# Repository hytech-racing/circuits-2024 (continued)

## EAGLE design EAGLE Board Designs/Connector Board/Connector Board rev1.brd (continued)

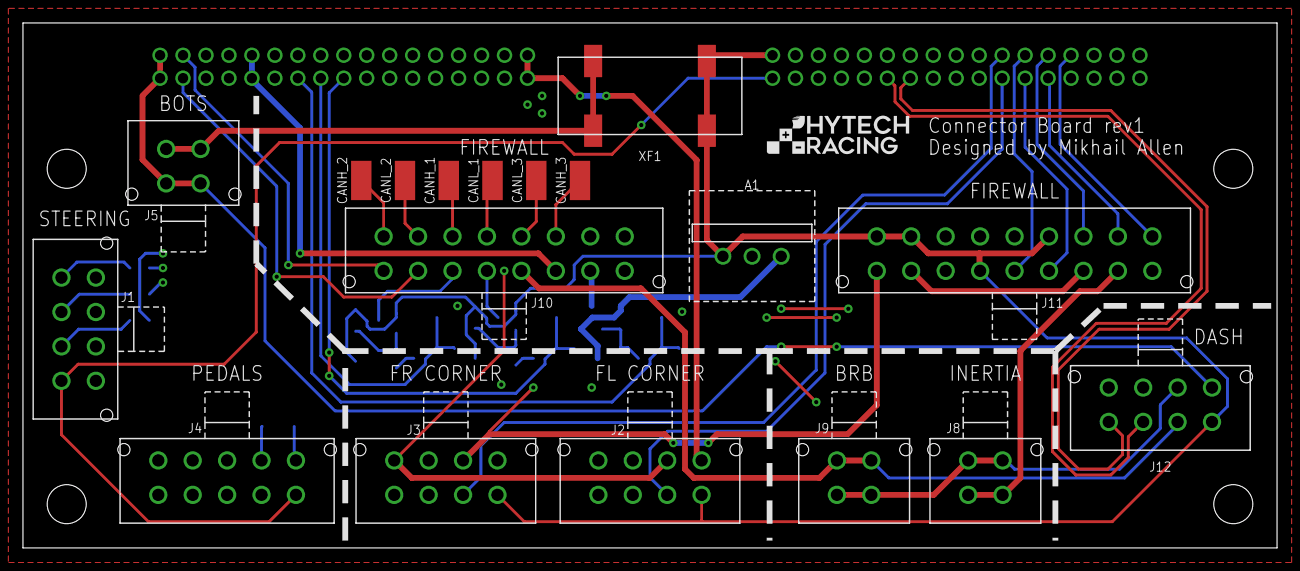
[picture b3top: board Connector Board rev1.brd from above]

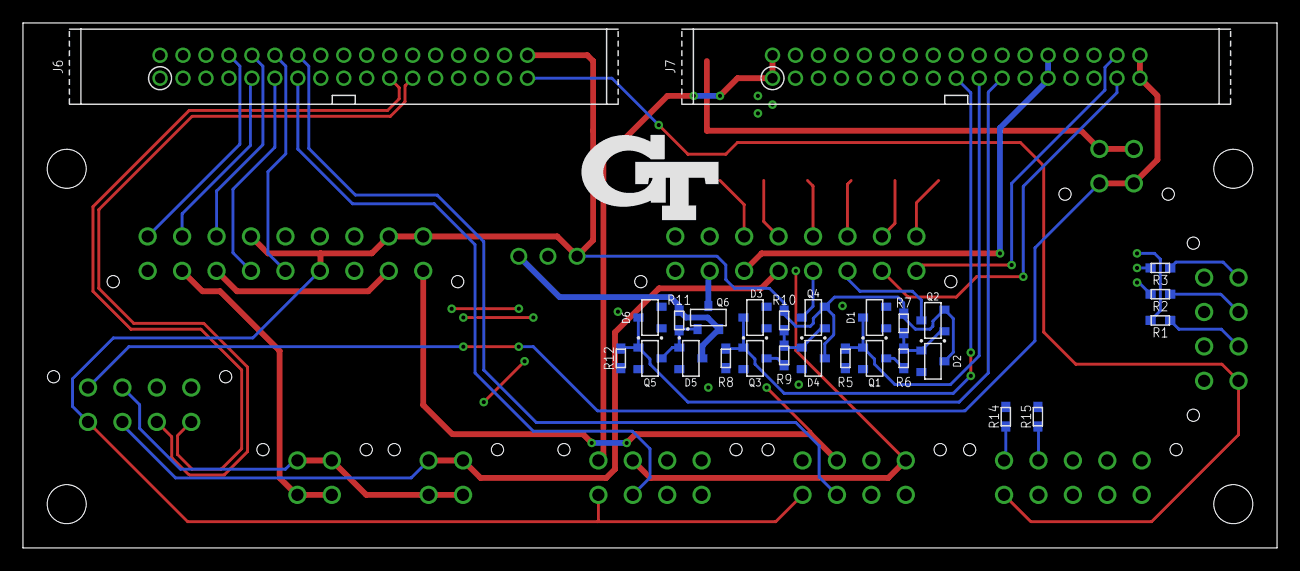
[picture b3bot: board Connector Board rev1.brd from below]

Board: 4 copper layers, 109.2 x 45.7 mm, 51 parts (28 on the bottom side), 59 nets.

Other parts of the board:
U$4, U$5, U$6, U$7: MOUNTING_M3
U$11: LOGO_GT_MEDIUM
U$14: LOGO_HYTECH_SMALL

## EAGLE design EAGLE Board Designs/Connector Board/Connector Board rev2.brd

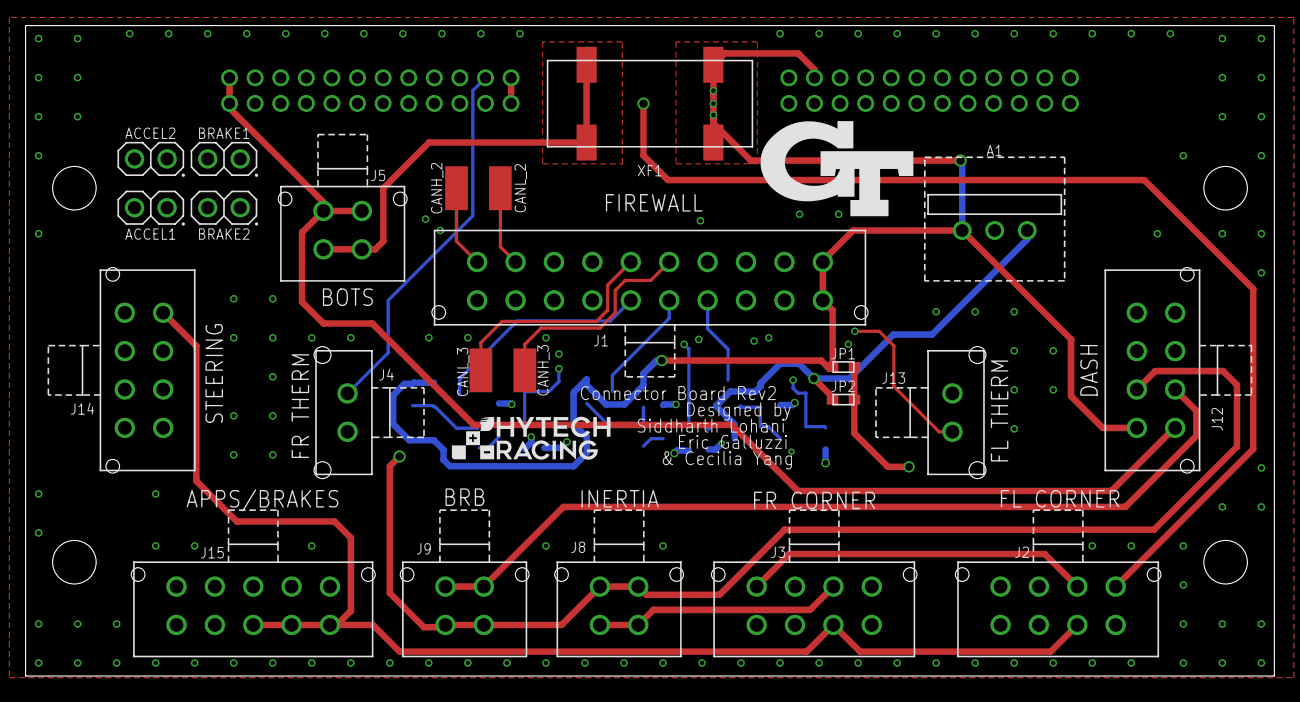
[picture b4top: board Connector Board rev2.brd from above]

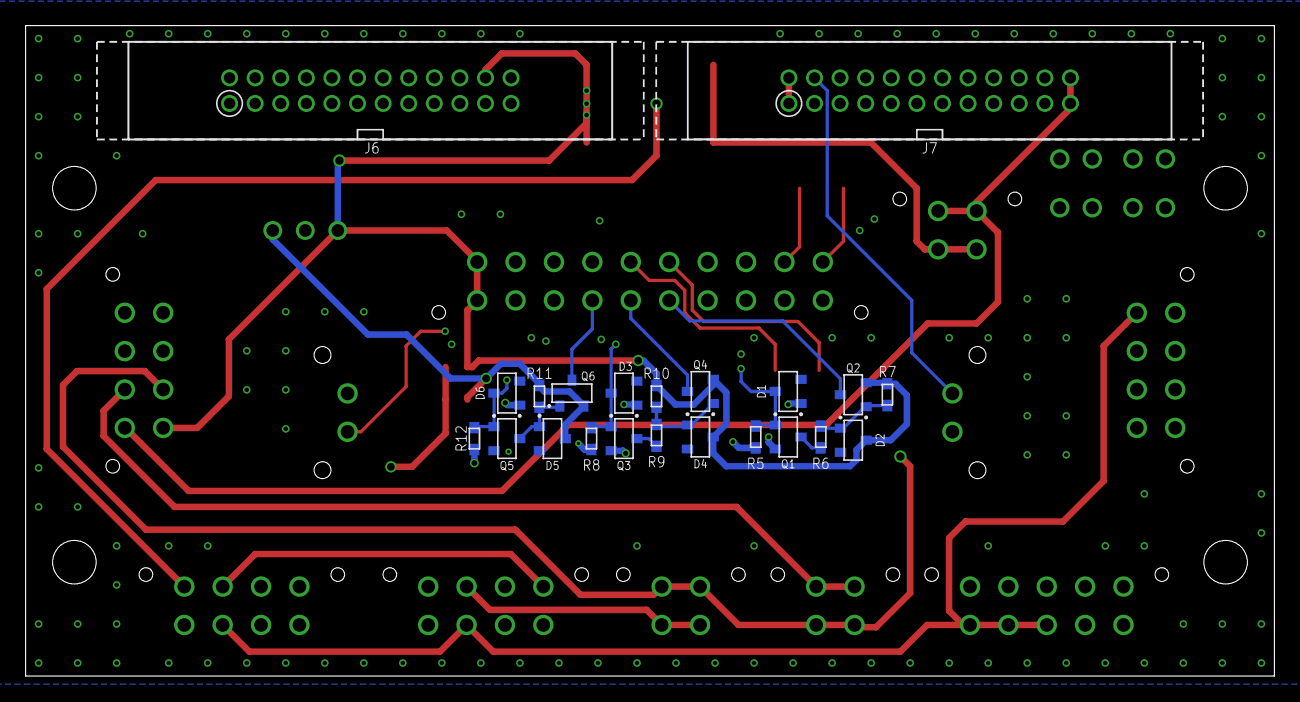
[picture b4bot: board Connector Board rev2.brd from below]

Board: 4 copper layers, 97.5 x 50.8 mm, 51 parts (22 on the bottom side), 52 nets.

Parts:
A1: VOLTAGE_REGULATOR_MODULE_OKI-78SR_12V; OKI-78SR
ACCEL1, ACCEL2: JUMPER__1X02; 1X02
BRAKE1, BRAKE2: JUMPER__1X02; 1X02
CANH_2, CANH_3: TEST_POINT; 5015
CANL_2, CANL_3: TEST_POINT; 5015
D1, D2, D3, D4, D5, D6: TVS__15V; SOT-23
J1: CONNECTOR-20_MF_T_V_; MOLEX_MICROFIT_PTH_VERTICAL_20_DUAL
J2, J3, J12, J14: CONNECTOR-8_μF_T_V_BLACK; MOLEX_MICROFIT_PTH_VERTICAL_08_DUAL
J4, J13: CONNECTOR-2_MF_T_V_; MOLEX_MICROFIT_PTH_VERTICAL_02_SINGLE
J5, J8, J9: CONNECTOR-4_μF_T_V_BLACK; MOLEX_MICROFIT_PTH_VERTICAL_04_DUAL
J6, J7: CONNECTOR-24_CONNECTOR-24_; EHT-112-01
J15: CONNECTOR-10_MF_T_V_; MOLEX_MICROFIT_PTH_VERTICAL_10_DUAL
JP1, JP2: JUMPER_0603_; 0603-RES
Q1, Q3, Q5: TRANSISTOR_N_MOS__DMG3406L-7; SOT-23
Q2, Q4, Q6: TRANSISTOR_P_MOS_SOT-23_DMP3056L-7; SOT-23
R5, R8, R11, R12: RESISTOR_0603_10K; 0603-RES
R6, R7, R9, R10: RESISTOR_0603_5.1K; 0603-RES
U$4, U$5, U$6, U$7: MOUNTING_M3
U$11: LOGO_GT_MEDIUM
U$14: LOGO_HYTECH_SMALL
XF1: FUSE_HOLDER_MINIBLADESMD; 3588

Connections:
+5V: J2.2, J3.2, J6.24, J14.1, J15.1, J15.2, J15.3
+12V: A1.3, D5.3, JP2.1, Q6.2, R11.2
+24V: A1.1, D2.3, D4.3, J1.10, J1.20, J6.22, J12.1, JP1.1, Q2.2, Q4.2, R7.2, R10.2, XF1.1, XF1.2
ACCEL_1_EXT: ACCEL1.2, J15.4
ACCEL_2_EXT: ACCEL2.2, J15.5
BMS_OK: J1.14, J7.7
BRAKELIGHT_12V: J1.17, Q6.3
BRAKELIGHT_EN: D6.3, J7.10, Q5.1, R12.2
BRAKE_1_EXT: BRAKE1.2, J15.7
BRAKE_2_EXT: BRAKE2.2, J15.6
CANH_2: CANH_2.1, J1.1, J1.4, J6.19
CANH_3: CANH_3.1, J1.6, J6.16, J12.3
CANL_2: CANL_2.1, J1.2, J1.3, J6.20
CANL_3: CANL_3.1, J1.5, J6.17, J12.4
CB_VIN: J2.1, J3.1, JP1.2, JP2.2
CURRENT_EXT: J1.12, J7.11
FL_CORNER_EXT_N: J2.4, J6.2
FL_CORNER_EXT_P: J2.3, J6.1
FR_CORNER_EXT_N: J3.4, J6.5
FR_CORNER_EXT_P: J3.3, J6.6
GND: A1.2, D1.1, D3.1, D6.1, J1.9, J1.19, J2.7, J3.7, J4.1, J6.3, J6.4, J6.7, J6.8, J6.11, J6.12, J6.15, J6.18, J6.21, J6.23, J12.8, J13.1, J14.8, J15.8, J15.9, J15.10, Q1.2, Q3.2, Q5.2, R5.1, R8.1, R12.1
INVERTER_24V_EN: D1.3, J7.8, Q1.1, R5.2
INVERTER_24V_EN_BOOSTED: J1.15, Q2.3
INVERTER_EN: D3.3, J7.6, Q3.1, R8.2
INVERTER_EN_BOOSTED: J1.16, Q4.3
LATCH_BTN: J1.18, J7.13, J7.14
unnamed: ACCEL1.1, J7.15
unnamed: ACCEL2.1, J7.16
unnamed: BRAKE2.1, J7.17
unnamed: BRAKE1.1, J7.18
unnamed: D2.1, Q2.1, R6.2, R7.1
unnamed: Q1.3, R6.1
unnamed: D4.1, Q4.1, R9.2, R10.1
unnamed: Q3.3, R9.1
unnamed: D5.1, Q5.3, Q6.1, R11.1
OKHS_IN: J1.13, J7.9
REFERENCE_EXT: J1.11, J7.12
SHDN_A: J5.1, J5.2, XF1.3, XF1.4
SHDN_B: J5.3, J5.4, J7.23, J7.24, J12.5
SHDN_G: J2.5, J7.1, J7.2
SHDN_H: J2.6, J3.8
SHDN_I: J3.6, J8.1, J8.2
SHDN_J: J7.5, J8.3, J8.4, J9.1, J9.2, J12.2
SHDN_K: J1.7, J1.8, J9.3, J9.4, J12.6
STEERING_1_EXT: J7.19, J14.7
STEERING_2_EXT: J7.20, J14.6
STEERING_RX_N: J6.14, J14.5
STEERING_RX_P: J6.13, J14.2
STEERING_TX_N: J6.10, J14.4
STEERING_TX_P: J6.9, J14.3
THERM_FL_EXT: J7.3, J13.2
THERM_FR_EXT: J4.2, J7.4

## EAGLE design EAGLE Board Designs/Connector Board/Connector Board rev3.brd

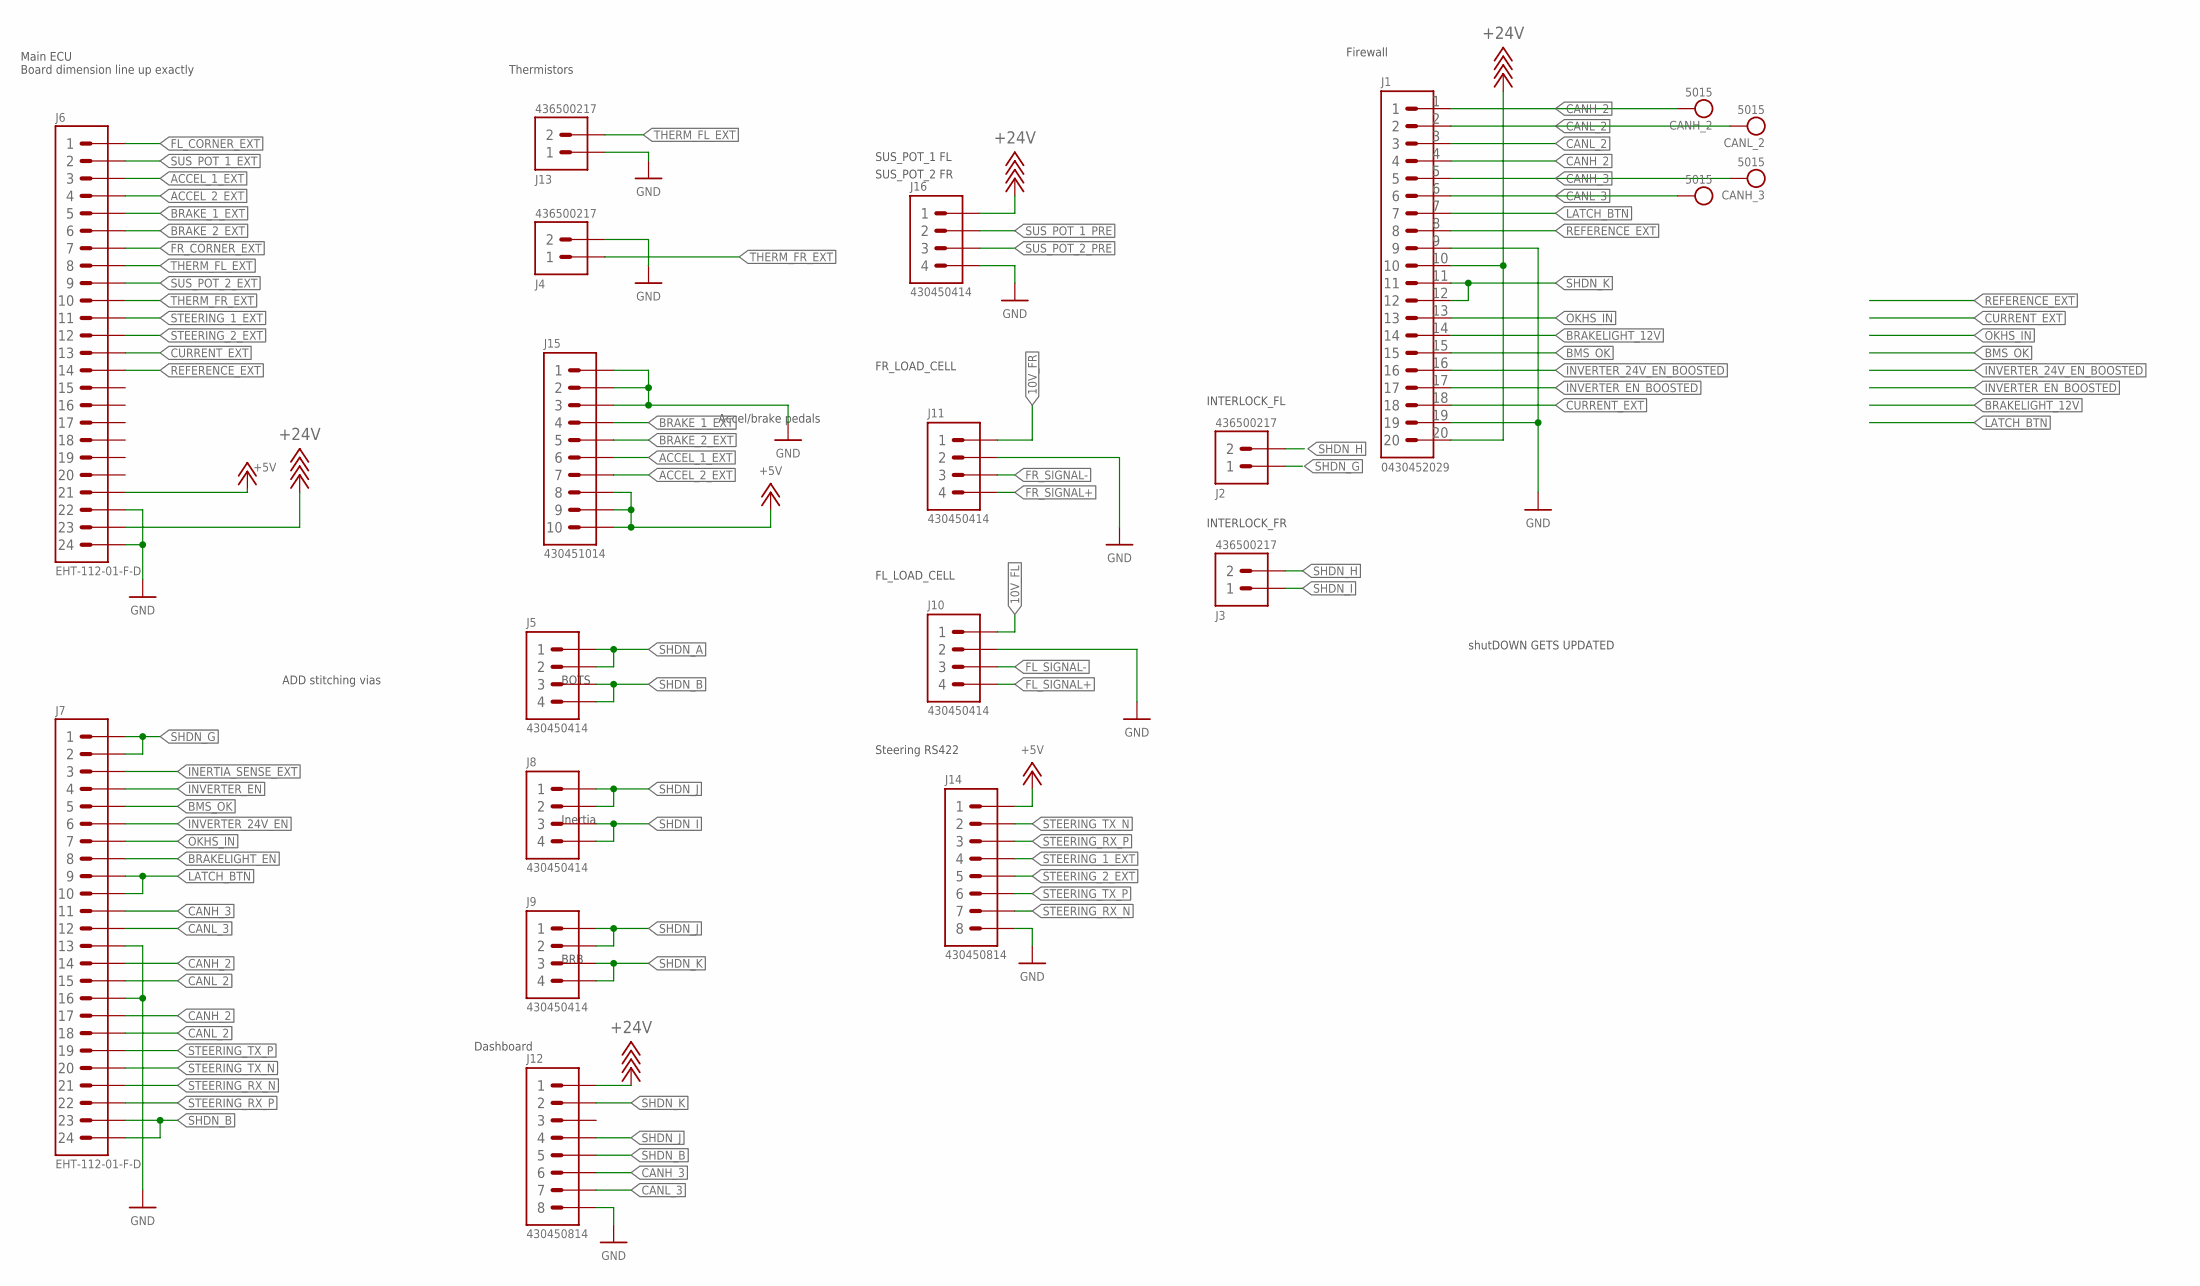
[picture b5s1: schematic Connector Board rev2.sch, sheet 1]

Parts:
CANH_2, CANH_3: TEST_POINT; 5015
CANL_2, CANL_3: TEST_POINT; 5015
J1: CONNECTOR-20_MF_T_V_; MOLEX_MICROFIT_PTH_VERTICAL_20_DUAL
J2, J3, J4, J13: CONNECTOR-2_MF_T_V_; MOLEX_MICROFIT_PTH_VERTICAL_02_SINGLE
J5, J8, J9, J10, J11, J16: CONNECTOR-4_μF_T_V_BLACK; MOLEX_MICROFIT_PTH_VERTICAL_04_DUAL
J6, J7: CONNECTOR-24_CONNECTOR-24_; EHT-112-01
J12, J14: CONNECTOR-8_μF_T_V_BLACK; MOLEX_MICROFIT_PTH_VERTICAL_08_DUAL
J15: CONNECTOR-10_MF_T_V_; MOLEX_MICROFIT_PTH_VERTICAL_10_DUAL

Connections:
10V_FL: J10.1; also elsewhere on the board
10V_FR: J11.1; also elsewhere on the board
+5V: J6.21, J14.1, J15.8, J15.9, J15.10
+24V: J1.10, J1.20, J6.23, J12.1, J16.1; also elsewhere on the board
ACCEL_1_EXT: J6.3, J15.6
ACCEL_2_EXT: J6.4, J15.7
BMS_OK: J1.15, J7.5
BRAKELIGHT_12V: J1.14; also elsewhere on the board
BRAKELIGHT_EN: J7.8; also elsewhere on the board
BRAKE_1_EXT: J6.5, J15.4
BRAKE_2_EXT: J6.6, J15.5
CANH_2: CANH_2.1, J1.1, J1.4, J7.14, J7.17
CANH_3: CANH_3.1, J1.5, J7.11, J12.6
CANL_2: CANL_2.1, J1.2, J1.3, J7.15, J7.18
CANL_3: CANL_3.1, J1.6, J7.12, J12.7
CURRENT_EXT: J1.18, J6.13
FL_CORNER_EXT: J6.1; also elsewhere on the board
FL_SIGNAL+: J10.4; also elsewhere on the board
FL_SIGNAL-: J10.3; also elsewhere on the board
FR_CORNER_EXT: J6.7; also elsewhere on the board
FR_SIGNAL+: J11.4; also elsewhere on the board
FR_SIGNAL-: J11.3; also elsewhere on the board
GND: J1.9, J1.19, J4.2, J6.22, J6.24, J7.13, J7.16, J10.2, J11.2, J12.8, J13.1, J14.8, J15.1, J15.2, J15.3, J16.4; also elsewhere on the board
INERTIA_SENSE_EXT: J7.3
INVERTER_24V_EN: J7.6; also elsewhere on the board
INVERTER_24V_EN_BOOSTED: J1.16; also elsewhere on the board
INVERTER_EN: J7.4; also elsewhere on the board
INVERTER_EN_BOOSTED: J1.17; also elsewhere on the board
LATCH_BTN: J1.7, J7.9, J7.10
OKHS_IN: J1.13, J7.7
REFERENCE_EXT: J1.8, J6.14
SHDN_A: J5.1, J5.2; also elsewhere on the board
SHDN_B: J5.3, J5.4, J7.23, J7.24, J12.5
SHDN_G: J2.1, J7.1, J7.2
SHDN_H: J2.2, J3.2
SHDN_I: J3.1, J8.3, J8.4
SHDN_J: J8.1, J8.2, J9.1, J9.2, J12.4
SHDN_K: J1.11, J1.12, J9.3, J9.4, J12.2
STEERING_1_EXT: J6.11, J14.4
STEERING_2_EXT: J6.12, J14.5
STEERING_RX_N: J7.21, J14.7
STEERING_RX_P: J7.22, J14.3
STEERING_TX_N: J7.20, J14.2
STEERING_TX_P: J7.19, J14.6
SUS_POT_1_EXT: J6.2; also elsewhere on the board
SUS_POT_1_PRE: J16.2; also elsewhere on the board
SUS_POT_2_EXT: J6.9; also elsewhere on the board
SUS_POT_2_PRE: J16.3; also elsewhere on the board
THERM_FL_EXT: J6.8, J13.2
THERM_FR_EXT: J4.1, J6.10

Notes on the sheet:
BOTS
Inertia
BRB
ADD stitching vias
Accel/brake pedals
Dashboard
Steering RS422
Firewall
Main ECU Board dimension line up exactly
Thermistors
shutDOWN GETS UPDATED
FL_LOAD_CELL
FR_LOAD_CELL
SUS_POT_1 FL
SUS_POT_2 FR
INTERLOCK_FL
INTERLOCK_FR

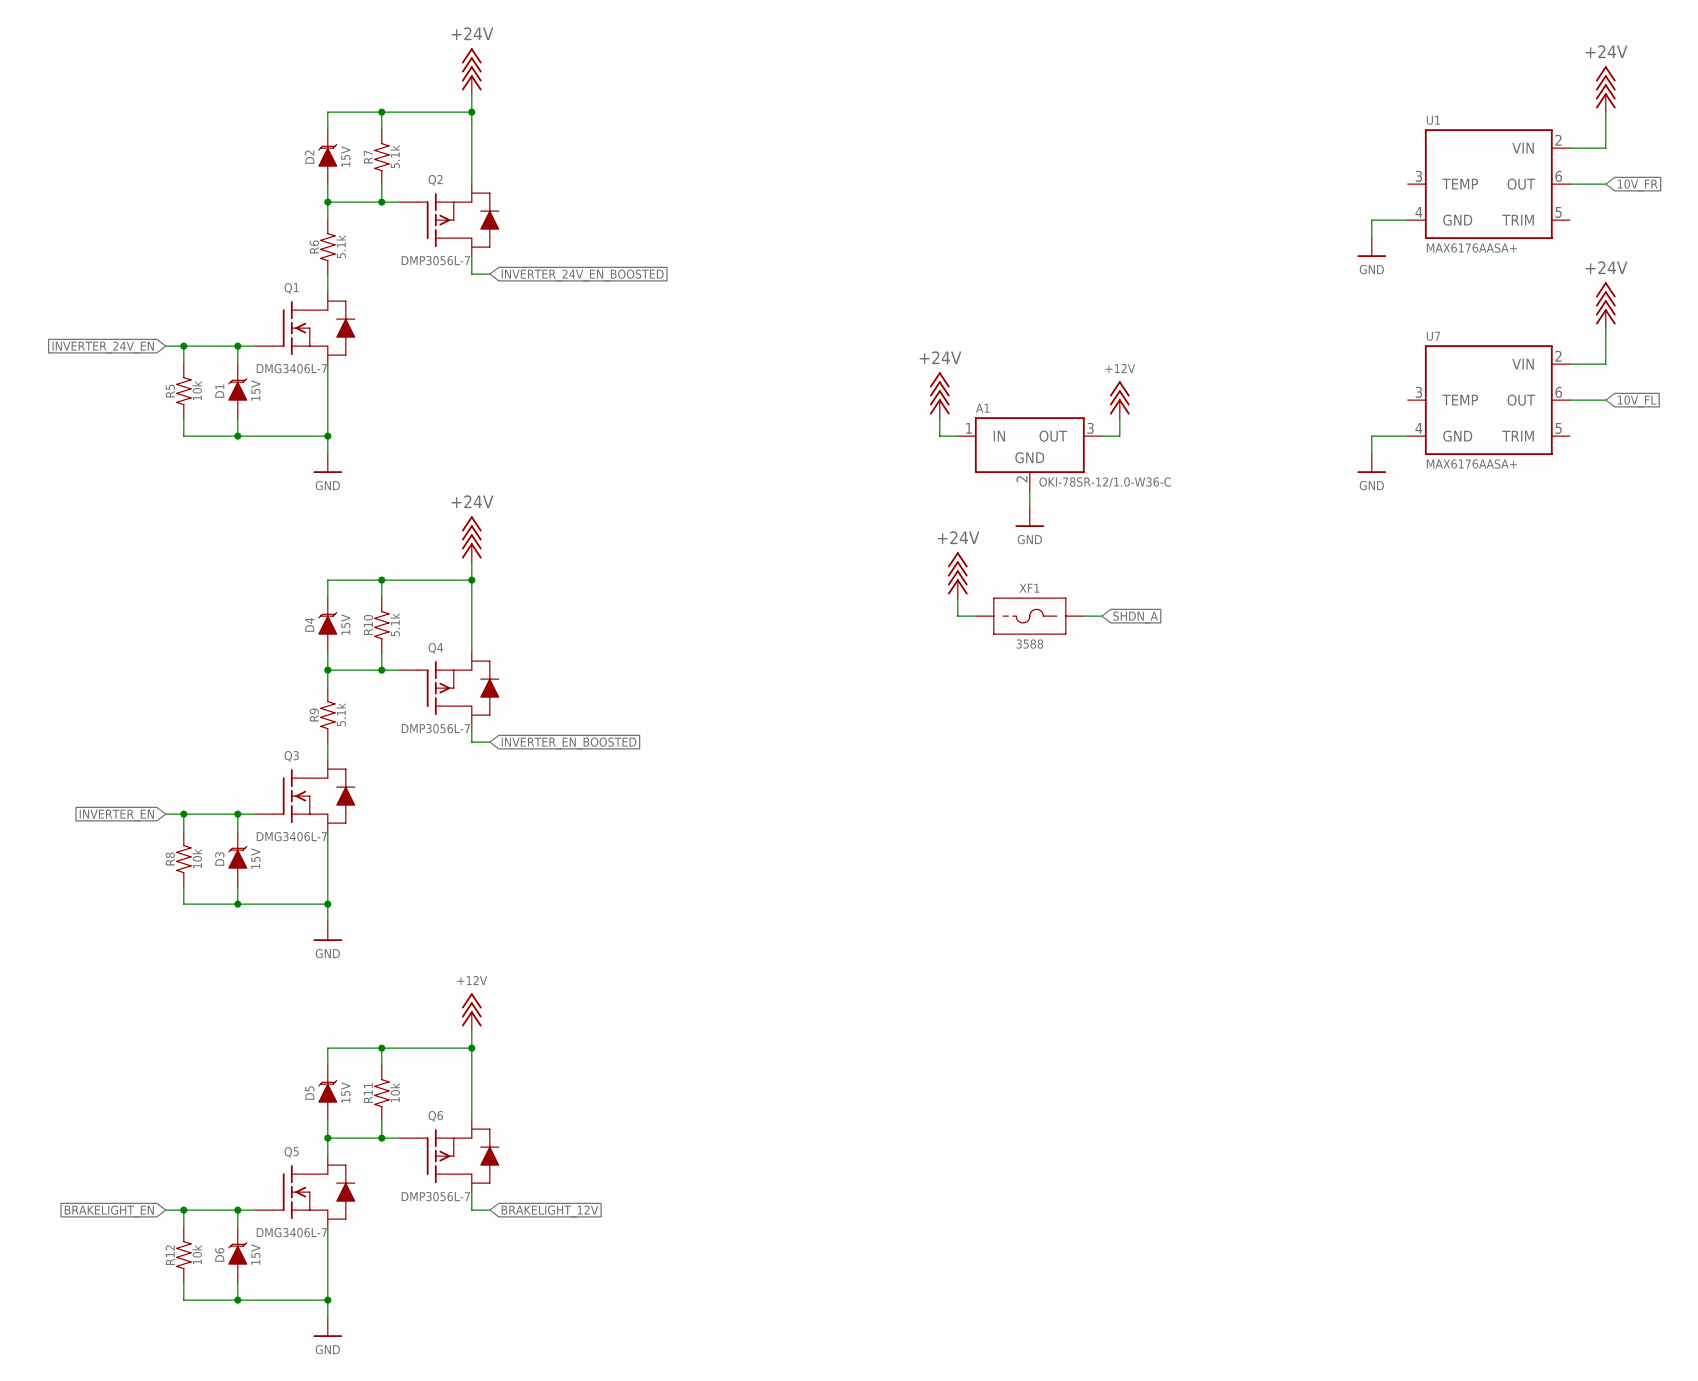
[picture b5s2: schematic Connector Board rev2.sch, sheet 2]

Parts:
A1: VOLTAGE_REGULATOR_MODULE_OKI-78SR_12V; OKI-78SR
D1, D2, D3, D4, D5, D6: TVS__15V; SOT-23
Q1, Q3, Q5: TRANSISTOR_N_MOS__DMG3406L-7; SOT-23
Q2, Q4, Q6: TRANSISTOR_P_MOS_SOT-23_DMP3056L-7; SOT-23
R5, R8, R11, R12: RESISTOR_0603_10K; 0603-RES
R6, R7, R9, R10: RESISTOR_0603_5.1K; 0603-RES
U1, U7: VOLTAGE_REFERENCE_SOIC-8_10V; SOIC-08(NARROW,0.15")
XF1: FUSE_HOLDER_MINIBLADESMD; 3588

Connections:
10V_FL: U7.6 (OUT); also elsewhere on the board
10V_FR: U1.6 (OUT); also elsewhere on the board
+12V: A1.3 (OUT), D5.3 (C), Q6.2 (S), R11.2; also elsewhere on the board
+24V: A1.1 (IN), D2.3 (C), D4.3 (C), Q2.2 (S), Q4.2 (S), R7.2, R10.2, U1.2 (VIN), U7.2 (VIN), XF1.1, XF1.2 (1); also elsewhere on the board
BRAKELIGHT_12V: Q6.3 (D); also elsewhere on the board
BRAKELIGHT_EN: D6.3 (C), Q5.1 (G), R12.2; also elsewhere on the board
GND: A1.2 (GND), D1.1 (A), D3.1 (A), D6.1 (A), Q1.2 (S), Q3.2 (S), Q5.2 (S), R5.1, R8.1, R12.1, U1.4 (GND), U7.4 (GND); also elsewhere on the board
INVERTER_24V_EN: D1.3 (C), Q1.1 (G), R5.2; also elsewhere on the board
INVERTER_24V_EN_BOOSTED: Q2.3 (D); also elsewhere on the board
INVERTER_EN: D3.3 (C), Q3.1 (G), R8.2; also elsewhere on the board
INVERTER_EN_BOOSTED: Q4.3 (D); also elsewhere on the board
unnamed: D2.1 (A), Q2.1 (G), R6.2, R7.1
unnamed: Q1.3 (D), R6.1
unnamed: D4.1 (A), Q4.1 (G), R9.2, R10.1
unnamed: Q3.3 (D), R9.1
unnamed: D5.1 (A), Q5.3 (D), Q6.1 (G), R11.1
SHDN_A: XF1.3 (2), XF1.4 (2); also elsewhere on the board

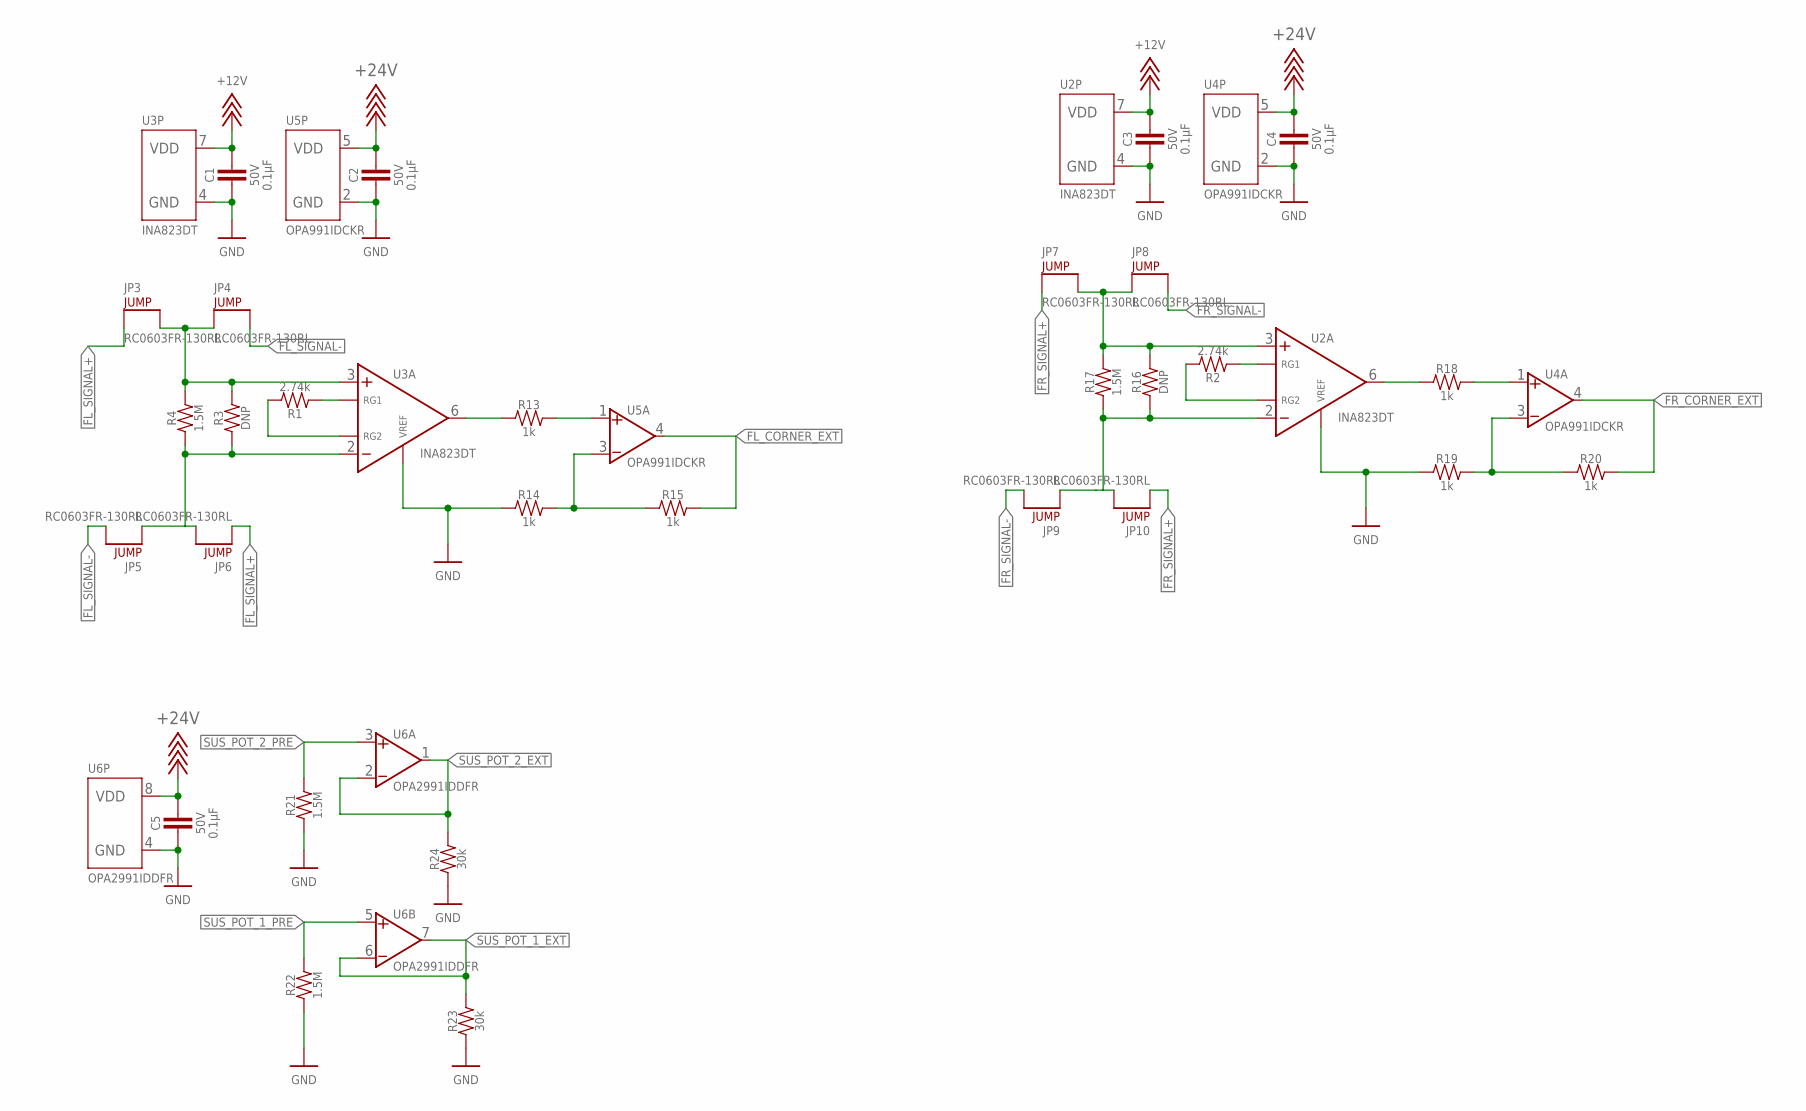
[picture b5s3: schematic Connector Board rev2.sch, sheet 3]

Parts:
C1, C2, C3, C4, C5: CAPACITOR_0603_50V_0.1UF; 0603-CAP
JP3, JP4, JP5, JP6, JP7, JP8, JP9, JP10: JUMPER_0603_; 0603-RES
R1, R2: RESISTOR_0603_2.74K; 0603-RES
R3, R16: RESISTOR_0603_DNP; 0603-RES
R4, R17, R21, R22: RESISTOR_0603_1.5M; 0603-RES
R13, R14, R15, R18, R19, R20: RESISTOR_0603_1K; 0603-RES
R23, R24: RESISTOR_0603_30K; 0603-RES
U2, U3: INA823DT; SOIC-08(NARROW,0.15")
U4, U5: OPAMP_1_CHANNEL_OPA991; SC-70-5
U6: OPAMP_2_CHANNEL_OPA_2991; SOT-23-8

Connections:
+12V: C1.1, C3.1, U2.7 (VDD), U3.7 (VDD); also elsewhere on the board
+24V: C2.1, C4.1, C5.1, U4.5 (VDD), U5.5 (VDD), U6.8 (VDD); also elsewhere on the board
FL_CORNER_EXT: R15.2, U5.4 (VOUT); also elsewhere on the board
FL_SIGNAL+: JP3.1, JP6.1; also elsewhere on the board
FL_SIGNAL-: JP4.2, JP5.2; also elsewhere on the board
FR_CORNER_EXT: R20.2, U4.4 (VOUT); also elsewhere on the board
FR_SIGNAL+: JP7.1, JP10.1; also elsewhere on the board
FR_SIGNAL-: JP8.2, JP9.2; also elsewhere on the board
GND: C1.2, C2.2, C3.2, C4.2, C5.2, R14.1, R19.1, R21.1, R22.1, R23.1, R24.1, U2.4 (GND), U2.5 (VREF), U3.4 (GND), U3.5 (VREF), U4.2 (GND), U5.2 (GND), U6.4 (GND); also elsewhere on the board
unnamed: R1.1, U3.1 (RG1)
unnamed: R1.2, U3.8 (RG2)
unnamed: R13.1, U3.6 (VOUT)
unnamed: R13.2, U5.1 (VIN+)
unnamed: JP3.2, JP4.1, R3.2, R4.2, U3.3 (VIN+)
unnamed: R14.2, R15.1, U5.3 (VIN-)
unnamed: R2.1, U2.1 (RG1)
unnamed: R2.2, U2.8 (RG2)
unnamed: JP7.2, JP8.1, R16.2, R17.2, U2.3 (VIN+)
unnamed: JP5.1, JP6.2, R3.1, R4.1, U3.2 (VIN-)
unnamed: R19.2, R20.1, U4.3 (VIN-)
unnamed: R18.1, U2.6 (VOUT)
unnamed: R18.2, U4.1 (VIN+)
unnamed: JP9.1, JP10.2, R16.1, R17.1, U2.2 (VIN-)
SUS_POT_1_EXT: R23.2, U6.6 (VIN-), U6.7 (VOUT); also elsewhere on the board
SUS_POT_1_PRE: R22.2, U6.5 (VIN+); also elsewhere on the board
SUS_POT_2_EXT: R24.2, U6.1 (VOUT), U6.2 (VIN-); also elsewhere on the board
SUS_POT_2_PRE: R21.2, U6.3 (VIN+); also elsewhere on the board

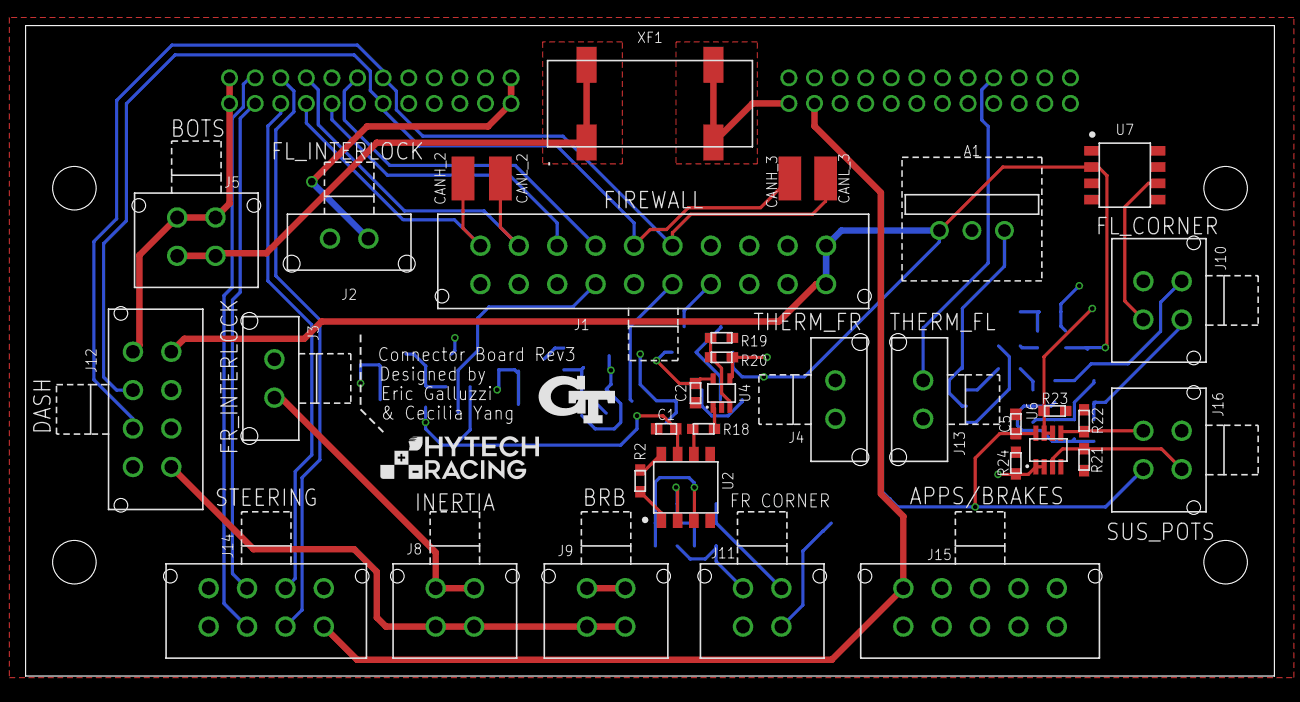
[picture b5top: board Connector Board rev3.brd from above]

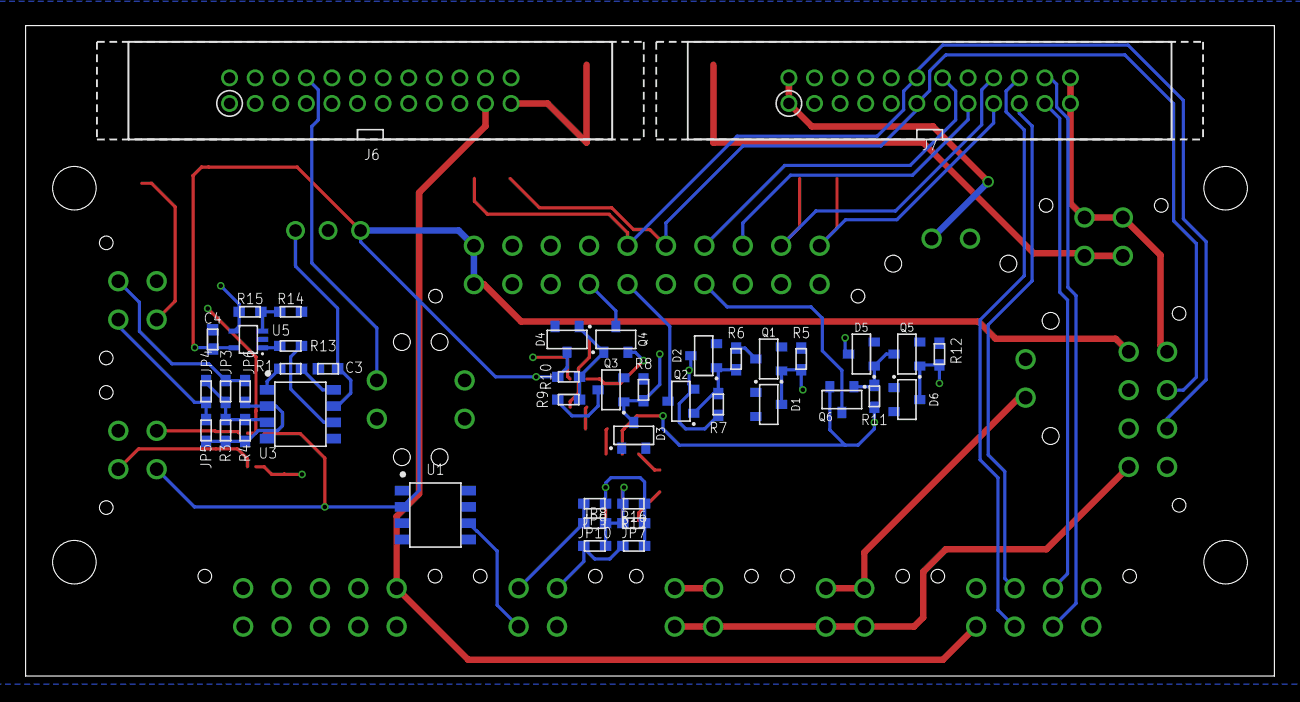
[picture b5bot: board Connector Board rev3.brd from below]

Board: 4 copper layers, 97.5 x 50.8 mm, 84 parts (43 on the bottom side), 69 nets.

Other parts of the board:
U$2: LOGO_GT_SMALL
U$4, U$5, U$6, U$7: MOUNTING_M3
U$14: LOGO_HYTECH_SMALL

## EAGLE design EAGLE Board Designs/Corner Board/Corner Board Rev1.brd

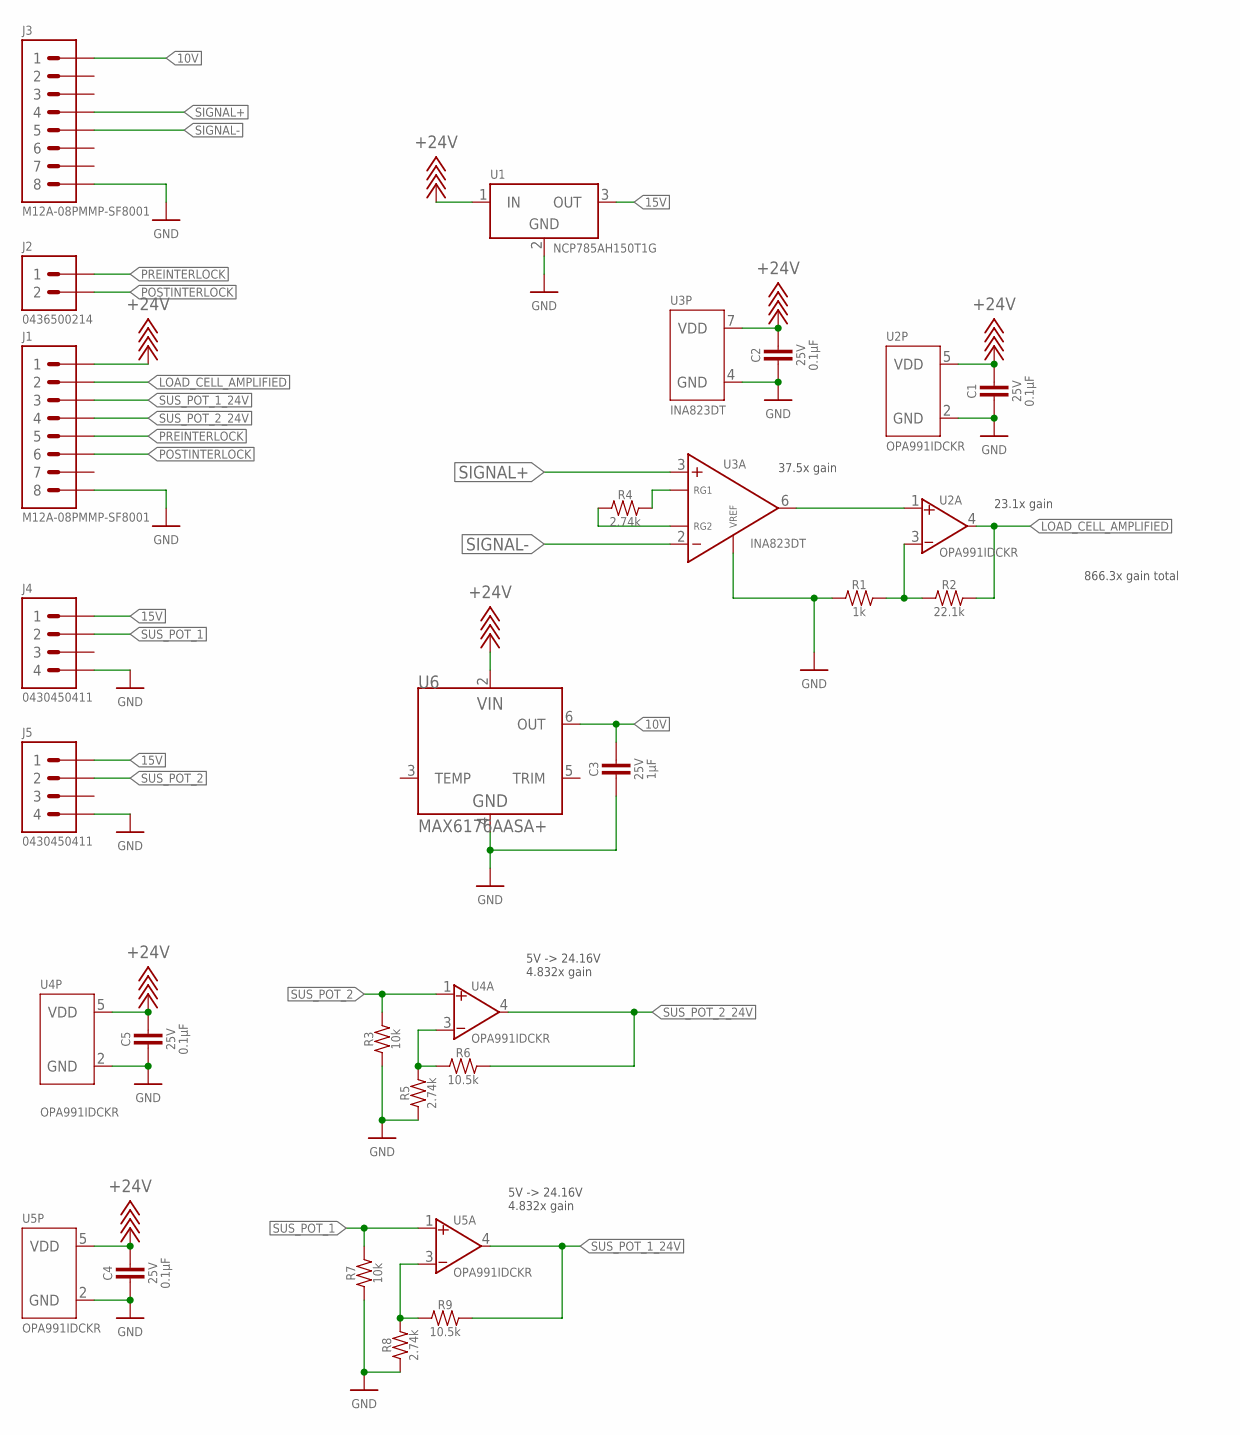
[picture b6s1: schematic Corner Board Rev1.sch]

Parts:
C1, C2, C4, C5: CAPACITOR_0603_25V_0.1UF; 0603-CAP
C3: CAPACITOR_0603_25V_1UF; 0603-CAP
J1, J3: CONNECTOR-8_AMPHENOL_M12A_08PMMP_; M12A-08PMMP
J2: CONNECTOR-2_MICROFIT_SMD_RIGHTANGLE_02_SINGLE_BLA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; MOLEX_MICROFIT_SMD_RIGHTANGLE_02_SINGLE
J4, J5: CONNECTOR-4_μF_S_RA_; MOLEX_MICROFIT_SMD_RIGHTANGLE_04_DUAL
R1: RESISTOR_0603_1K; 0603-RES
R2: RESISTOR_0603_22.1K; 0603-RES
R3, R7: RESISTOR_0603_10K; 0603-RES
R4, R5, R8: RESISTOR_0603_2.74K; 0603-RES
R6, R9: RESISTOR_0603_10.5K; 0603-RES
U1: VOLTAGE_REGULATOR_SOT-89_15V; SOT-89
U2, U4, U5: OPAMP_1_CHANNEL_OPA991; SC-70-5
U3: INA823DT; SOIC-08(NARROW,0.15")
U6: VOLTAGE_REFERENCE__10V; SOIC-08(NARROW,0.15")

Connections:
10V: C3.1, J3.1, U6.6 (OUT)
15V: J4.1, J5.1, U1.3 (OUT)
+24V: C1.1, C2.1, C4.1, C5.1, J1.1, U1.1 (IN), U2.5 (VDD), U3.7 (VDD), U4.5 (VDD), U5.5 (VDD), U6.2 (VIN)
GND: C1.2, C2.2, C3.2, C4.2, C5.2, J1.8, J3.8, J4.4, J5.4, R1.1, R3.1, R5.1, U1.2 (GND), U2.2 (GND), U3.4 (GND), U3.5 (VREF), U4.2 (GND), U5.2 (GND), U6.4 (GND)
LOAD_CELL_AMPLIFIED: J1.2, R2.2, U2.4 (VOUT)
unnamed: R1.2, R2.1, U2.3 (VIN-)
unnamed: R4.2, U3.1 (RG1)
unnamed: U2.1 (VIN+), U3.6 (VOUT)
unnamed: R4.1, U3.8 (RG2)
unnamed: R5.2, R6.1, U4.3 (VIN-)
unnamed: R7.1, R8.1
unnamed: R8.2, R9.1, U5.3 (VIN-)
POSTINTERLOCK: J1.6, J2.2
PREINTERLOCK: J1.5, J2.1
SIGNAL+: J3.4, U3.3 (VIN+)
SIGNAL-: J3.5, U3.2 (VIN-)
SUS_POT_1: J4.2, R7.2, U5.1 (VIN+)
SUS_POT_1_24V: J1.3, R9.2, U5.4 (VOUT)
SUS_POT_2: J5.2, R3.2, U4.1 (VIN+)
SUS_POT_2_24V: J1.4, R6.2, U4.4 (VOUT)

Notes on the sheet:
5V -> 24.16V 4.832x gain
37.5x gain
23.1x gain
866.3x gain total

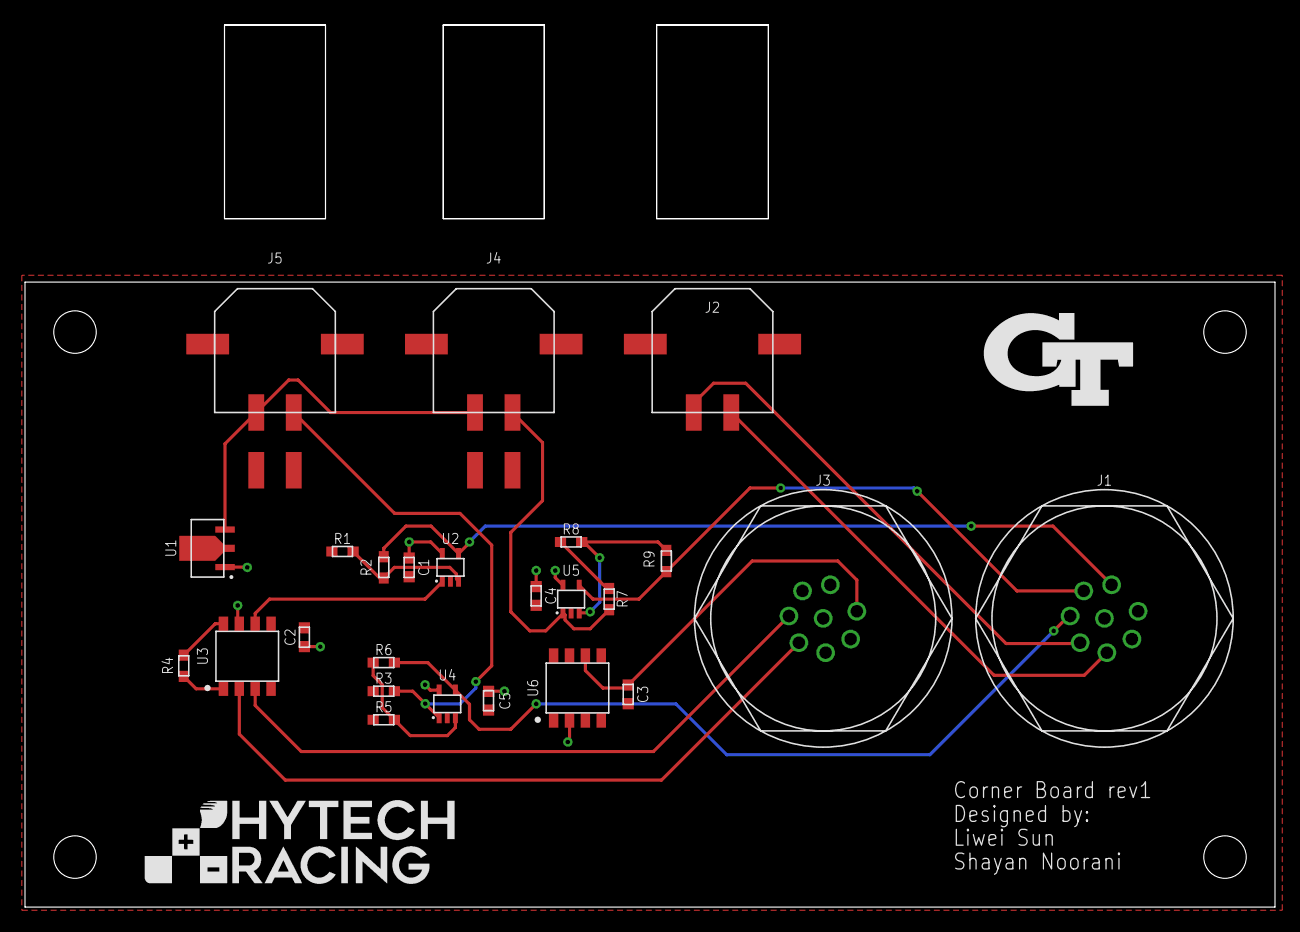
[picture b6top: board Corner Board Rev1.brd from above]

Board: 2 copper layers, 100.0 x 50.0 mm, 31 parts (0 on the bottom side), 20 nets.

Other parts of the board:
U$7, U$8, U$9, U$10: MOUNTING_M3
U$13: LOGO_HYTECH_MEDIUM
U$14: LOGO_GT_MEDIUM
